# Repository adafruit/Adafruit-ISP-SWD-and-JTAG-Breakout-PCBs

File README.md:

## Adafruit SWD and JTAG Breakout PCBs

<a href="http://www.adafruit.com/products/1465">&nbsp; 
<a href="http://www.adafruit.com/products/2094">&nbsp; 
<a href="http://www.adafruit.com/products/2743"><br/>
Click an image to purchase from the Adafruit shop</a>

PCB files for the Adafruit ISP, SWD and JTAG Breakouts. Format is EagleCAD schematic and board layout

For more details, check out the product pages at
* https://www.adafruit.com/products/1465 (AVR ISP)
* https://www.adafruit.com/products/2094 (JTAG to SWD)
* https://www.adafruit.com/products/2743 (SWD breakout)

### Descriptions

**AVR ISP:** It's rare to find a mini kit so elegant, it deserves its own Haiku. A simple breakout, 2x3 box header in the center, two 1x3's on the side. Plugs into any breadboard for neat wiring (in both nifty and clean senses of the word).

Comes with a quality mini PCB, a 2x3 box header and a small stick of 0.1" header. Requires some light soldering to use: plug the 2x3 in on the top and solder all six pins, then break the header in half and put each half into a breadboard to hold them steady. Place the breakout on top and solder the side pins. Will last you years and years.

**JTAG to SWD:** This adapter board is designed for adapting a 'classic' 2x10 (0.1"/2.54mm pitch) JTAG cable to a slimmer 2x5 (0.05"/1.27mm pitch) SWD Cable.  It's helpful for using products like the JTAGulator or SEGGER J-Link with tiny boards that use the 10-pin SWD programming connector.

This board comes with no cables.  It's really just the adapter - but is super helpful when you want to use JTAG debugging on boards that can't support 2x10 cables.

**SWD Breakout:** This adapter board is designed to make it easier to use ARM dev boards that use slimmer 2x5 (0.05"/1.27mm pitch) SWD cables for programming.  It's helpful for using products like the JTAGulator, STLink or SEGGER J-Link with tiny boards that use the 10-pin SWD programming connector, often Cortex M0 or M3's.

### License

Adafruit invests time and resources providing this open source design, please support Adafruit and open-source hardware by purchasing products from [Adafruit](https://www.adafruit.com)!

Designed by Limor Fried/Ladyada for Adafruit Industries.

Creative Commons Attribution/Share-Alike, all text above must be included in any redistribution. See license.txt for additional details.

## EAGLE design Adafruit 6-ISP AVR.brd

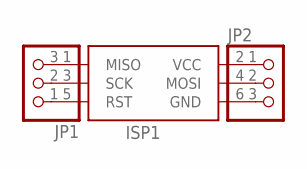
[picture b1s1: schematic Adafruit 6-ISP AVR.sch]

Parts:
ISP1: AVRISP-BOX
JP1, JP2: PINHD-1X3CB; 1X03-CLEANBIG

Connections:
GND: ISP1.6 (GND), JP2.3
MISO: ISP1.1 (MISO), JP1.3
MOSI: ISP1.4 (MOSI), JP2.2
RST: ISP1.5 (RST), JP1.1
SCK: ISP1.3 (SCK), JP1.2
VCC: ISP1.2 (VCC), JP2.1

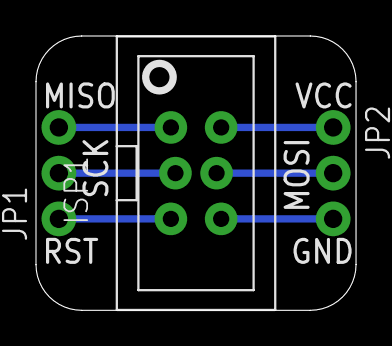
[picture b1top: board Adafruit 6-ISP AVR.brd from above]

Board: 2 copper layers, 17.8 x 15.2 mm, 4 parts (1 on the bottom side), 6 nets.

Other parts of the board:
U$1: ADAFRUIT_3.5MM

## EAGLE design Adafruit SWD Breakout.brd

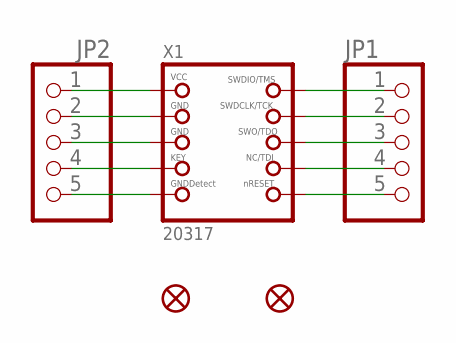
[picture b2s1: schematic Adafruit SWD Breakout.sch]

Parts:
FID1, FID2: FIDUCIAL""; FIDUCIAL_1MM
JP1, JP2: HEADER-1X576MIL_FULL; 1X05_ROUND_FULL_76
X1: 20317; 2X05_1.27MM_BOX_POSTS

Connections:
unnamed: JP2.1, X1.1 (VCC)
unnamed: JP2.2, X1.3 (GND)
unnamed: JP2.3, X1.5 (GND)
unnamed: JP2.4, X1.7 (KEY)
unnamed: JP2.5, X1.9 (GNDDETECT)
unnamed: JP1.1, X1.2 (SWDIO)
unnamed: JP1.2, X1.4 (SWDCLK)
unnamed: JP1.3, X1.6 (SWO)
unnamed: JP1.4, X1.8 (TDI)
unnamed: JP1.5, X1.10 (NRESET)

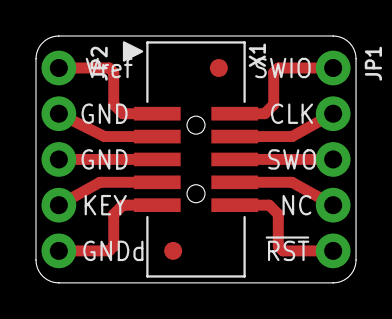
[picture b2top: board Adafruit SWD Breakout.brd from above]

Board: 2 copper layers, 17.8 x 13.7 mm, 6 parts (1 on the bottom side), 10 nets.

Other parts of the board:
U$2: ADAFRUIT_2.5MM

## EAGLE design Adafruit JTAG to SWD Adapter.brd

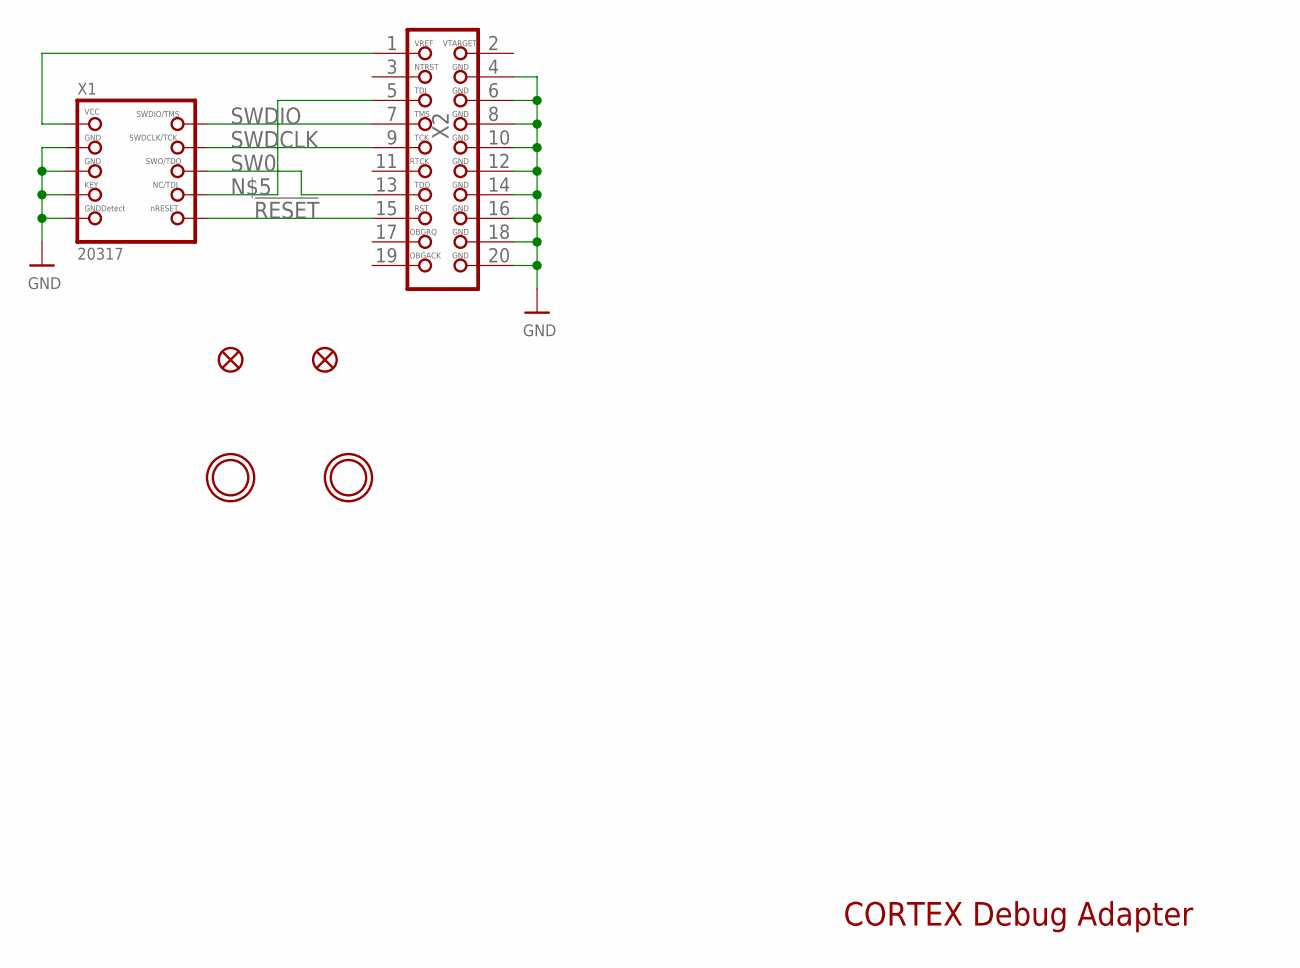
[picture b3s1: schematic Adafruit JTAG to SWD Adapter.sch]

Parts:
FID1, FID2: FIDUCIAL""; FIDUCIAL_1MM
U$5, U$6: MOUNTINGHOLE2.5; MOUNTINGHOLE_2.5_PLATED
X1: 20317; 2X05_1.27MM_BOX_POSTS
X2: 03587; 2X10_SMT_FEMALE

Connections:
!RESET: X1.10 (NRESET), X2.15
GND: X1.3 (GND), X1.5 (GND), X1.7 (KEY), X1.9 (GNDDETECT), X2.4, X2.6, X2.8, X2.10, X2.12, X2.14, X2.16, X2.18, X2.20
unnamed: X1.8 (TDI), X2.5
SW0: X1.6 (SWO), X2.13
SWDCLK: X1.4 (SWDCLK), X2.9
SWDIO: X1.2 (SWDIO), X2.7
VCC: X1.1 (VCC), X2.1

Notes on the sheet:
CORTEX Debug Adapter

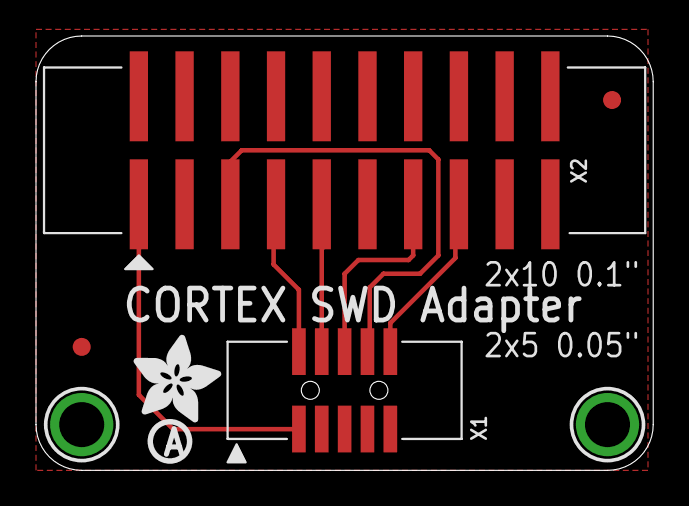
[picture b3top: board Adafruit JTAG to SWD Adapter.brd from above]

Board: 2 copper layers, 34.3 x 24.1 mm, 8 parts (0 on the bottom side), 7 nets.

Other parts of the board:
U$3: ADAFRUIT_5MM
U$4: PCBFEAT-REV-056

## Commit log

2016-06-27 initag
2016-09-23 best place for this

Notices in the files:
parts and their libraries:
microbuilder: This work is placed in the public domain, and may be freely used for commercial and non-commercial work with the following conditions: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
